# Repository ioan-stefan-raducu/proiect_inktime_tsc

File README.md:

# Proiect TSC 2026 - InkTime

Răducu Ioan Ștefan 335CA

## Descriere proiect
InkTime este un dispozitiv open source de tip smartwatch construit în cadrul clasei de proiectare hardware din UNSTPB. Device-ul are integrat un MCU nRF52840, senzori IMU și un display E-paper într-o carcasă compactă. Designul consideră aspectele legate de consum minim de energie și optimizarea PCB-ului pentru producție.

## Schema bloc

Se pot vedea în schema bloc componentele conectate prin săgeți. Săgețile au următoarele semnificații:
- **roșu** - trasee de putere
- **albastru deschis** - conexiuni I2C
- **albastru închis** - conexiuni SPI
- **mov** - trasee diferențiale
- **gri** - conexiuni GPIO sau fără a aparține categoriilor de mai sus

## Bill of Materials

| Componentă / Valoare | Cant. | Capsulă | Producător / Part Number | Sursă Achiziție (JLC/Mouser) | Datasheet |
| :--- | :---: | :--- | :--- | :--- | :--- |
| **nRF52840** | 1 | aQFN-73 | Nordic / nRF52840-QIAA | [Mouser Link](https://www.mouser.ro/c/?q=nRF52840) | [Datasheet](https://infocenter.nordicsemi.com/pdf/nRF52840_PS_v1.1.pdf) |
| **BMA423** | 1 | 12-pin LGA | Bosch / BMA423 | [Mouser Link](https://www.mouser.co.uk/ProductDetail/Bosch-Sensortec/BMA423?qs=HXFqYaX1Q2xC%252BSgeGoX3mg%3D%3D) | [Datasheet](https://www.bosch-sensortec.com/media/boschsensortec/downloads/datasheets/bst-bma423-ds004.pdf) |
| **BQ25180YBGR** | 1 | BGA-8 | TI / BQ25180YBGR | [Mouser Link](https://www.mouser.co.uk/ProductDetail/Texas-Instruments/BQ25180YBGR?qs=doiCPypUmgEWjAK%252BJAX6Tw%3D%3D) | [Datasheet](https://www.ti.com/lit/ds/symlink/bq25180.pdf) |
| **MAX17048G+T10** | 1 | TDFN-8 | Analog Devices / MAX17048 | [Mouser Link](https://www.mouser.ro/Search/Refine?Keyword=MAX17048G%2BT10) | [Datasheet](https://datasheets.maximintegrated.com/en/ds/MAX17048-MAX17049.pdf) |
| **DRV2605YZFR** | 1 | BGA-9 | TI / DRV2605YZFR | [Mouser Link](https://www.mouser.ro/Search/Refine?Keyword=DRV2605YZFR) | [Datasheet](https://www.ti.com/lit/ds/symlink/drv2605.pdf) |
| **RT6160AWSC** | 1 | WLCSP-15 | Richtek / RT6160AWSC | [Mouser Link](https://www.mouser.co.uk/ProductDetail/Richtek/RT6160AWSC?qs=amGC7iS6iy%2FLd9PSoixZXQ%3D%3D) | [Datasheet](https://www.richtek.com/assets/product_file/RT6160/DS6160-03.pdf) |
| **2450AT18B100E** | 1 | 3216 (1206) | Johanson / Antenă 2.45GHz | [Mouser Link](https://www.mouser.co.uk/ProductDetail/Johanson-Technology/2450AT18B100E?qs=yCnrNFeXz%252Bh5MFsFIXGZGA%3D%3D) | [Datasheet](https://www.johansontechnology.com/datasheets/2450AT18B100E/2450AT18B100E.pdf) |
| **744043680 (L4)** | 1 | 4.8x4.8mm | Wurth / 68µH Inductor | [JLC Part](https://jlcpcb.com/partdetail/Wurth_Elektronik-744043680/C167448) | [Datasheet](https://www.we-online.com/catalog/datasheet/744043680.pdf) |
| **FTC252012SR47** | 1 | 2520 (1008) | TDK / 0.47µH Inductor | [JLC Part (C5832368)](https://jlcpcb.com/partdetail/6763488-FTC252012SR47MBCA/C5832368) | [Datasheet](https://product.tdk.com/en/system/files/dam/doc/product/inductor/inductor/smd/catalog/inductor_commercial_power_ftc252012s_en.pdf) |
| **503480-2400** | 1 | FPC-24 | Molex / Conector EPD | [Mouser Link](https://www.mouser.co.uk/ProductDetail/Molex/503480-2400?qs=OAhjpuo3Vu7efIoxFh9AOw%3D%3D) | [Datasheet](https://www.molex.com/pdm_docs/sd/5034802400_sd.pdf) |
| **USB-C 16P** | 1 | SMT | Kinghelm / KH-TYPE-C-16P | [JLC Part](https://jlcpcb.com/partdetail/Kinghelm-KH_TYPE_C_16P/C5186522) | [Datasheet](https://datasheet.lcsc.com/lcsc/2112151030_Kinghelm-KH-TYPE-C-16P_C2930266.pdf) |
| **EVP-AKE31A** | 3 | SMT (Buton) | Panasonic / Tactile SW | [Mouser Link](https://www.mouser.ro/Search/Refine?Keyword=EVP-AKE31A) | [Datasheet](https://industrial.panasonic.com/ww/products/pt/tactile-sw/models/EVPAKE31A) |
| **USBLC6-2SC6Y** | 1 | SOT-23-6 | ST / Protecție ESD | [JLC Part](https://jlcpcb.com/partdetail/STMicroelectronics-USBLC6_2SC6Y/C7519) | [Datasheet](https://www.st.com/resource/en/datasheet/usblc6-2.pdf) |
| **MBR0530** | 3 | SOD-123 | ON Semi / Schottky 0.5A | [JLC Part](https://jlcpcb.com/partdetail/onsemi-MBR0530T1G/C2131) | [Datasheet](https://www.onsemi.com/pdf/datasheet/mbr0530t1-d.pdf) |
| **SI1308EDL** | 1 | SC-70-3 | Vishay / N-Ch MOSFET | [Mouser Link](https://www.mouser.ro/Search/Refine?Keyword=SI1308EDL) | [Datasheet](https://www.vishay.com/docs/72013/si1308edl.pdf) |
| **DMG2305UX-7** | 1 | SOT-23 | Diodes Inc / P-Ch MOSFET | [JLC Part](https://jlcpcb.com/partdetail/Diodes_Incorporated-DMG2305UX_7/C128526) | [Datasheet](https://www.diodes.com/assets/Datasheets/DMG2305UX.pdf) |

### Rezistente si condensatoare

| Valoare | Cant. | Capsulă | Tip | JLC |
| :--- | :---: | :--- | :--- | :--- |
| **1uF / 50V** | 10 | 0402 | Condensator (EPD) | [C52923](https://jlcpcb.com/partdetail/Samsung_Electro_Mechanics-CL05A105KB5NQNC/C52923) |
| **10uF** | 4 | 0402 | Condensator | [C15525](https://jlcpcb.com/partdetail/Samsung_Electro_Mechanics-CL05A106MQ5NUNC/C15525) |
| **100nF** | 5 | 0201 | Condensator | [C1619](https://jlcpcb.com/partdetail/Murata_Electronics-GRM033R61A104KE84D/C1619) |
| **10K** | 6 | 0201 | Rezistență | [C25744](https://jlcpcb.com/partdetail/Yageo-RC0201JR_0710KL/C25744) |
| **5.1K (5K1)** | 2 | 0201 | Rezistență (USB CC) | [C25785](https://jlcpcb.com/partdetail/Yageo-RC0201JR_075K1L/C25785) |
| **3.3K (3K3)** | 2 | 0201 | Rezistență | [C25891](https://jlcpcb.com/partdetail/Yageo-RC0201JR_073K3L/C25891) |

## Funcționalități hardware

Pentru următoarele funcționalități hardware se vor folosi numele circuitelor așa cum sunt reprezentate în schematic. La conectarea cu alte circuite se vor menționa circuitele cu semnalele puse în paranteză, lângă menționarea lor.

### LiPo Battery
Circuitul LiPo battery este conectorul către baterie. El este amplasat aproape de circuitul **DC/DC (VREG, 3V3)** și **Fuel Gauge (3V3, VBAT)**, formând un ansamblu. Acest ansamblu este amplasat lângă **E-Paper Connector** și **USB Connector (VBUS)** pentru a izola zonele care se ocupă cu traseele de putere sau au putere mare de restul componentelor, pentru a evita interferențele. Este conectat la microcontroler prin protocolul I2C.

### Fuel Gauge
Circuitul Fuel Gauge se ocupă cu măsurarea nivelului bateriei și alertarea microprocesorului când bateria este descărcată. El este conectat la microcontroler prin protocolul I2C și semnalul **ALERT** (probabil folosit ca întrerupere).

### DC/DC
Circuitul DC/DC este adaptorul de tensiune al PCB-ului. El trimite semnale de putere folosind PWM pentru a regla tensiunea. Este conectat la procesor prin protocolul I2C.

### E-Paper Connector
Circuitul E-Paper Connector este conexiunea la ecranul E-Paper. El este conectat la microcontroler prin protocolul SPI. Semnalele care sunt conectate la microcontroler sunt **EPD_BUSY, EPD_RST, EPD_DC, EPD_CS, SCK și MOSI**. El este conectat și la circuitul **E-Paper Drive Circuit** prin PREVGH, PREVGL și 3V3.

### E-Paper Drive Circuit
Circuitul E-Paper Drive "crește” semnalul pentru modelarea cernelii pentru ecranul E-Paper. El este plasat direct lângă **E-Paper Display Connector** datorită semnalului puternic de putere (până la 50V) pe care îl transmite ecranului. Astfel, ansamblul de putere menționat mai devreme, conectorul E-Paper și acest circuit sunt puse apropiat pentru a nu interfera cu restul PCB-ului.

### USB-C Connector
Circuitul USB-C Connector reprezintă mufa USB. Este conectat la ansamblul de putere (VBUS) și la circuitul **ESD Protection (VBUS, DN, DP)**. Deși în designul PCB-ului DN și DP ar trebui să fie trasee diferențiale, ele nu sunt. Am luat această decizie datorită poziției apropiate a USB-C Connector față de circuitul ESD Protection. El este conectat la microcontroler prin semnalul VBUS și indirect, prin ESD Protection, prin semnalele diferențiale D+ și D-.

### ESD Protection
Circuitul ESD Protection reprezintă protecția mufei USB-C în cazul descărcărilor statice. El este conectat la **USB-C Connector (VBUS, DN, DP)** și la microcontroler (D+, D- trasee diferențiale). În designul PCB-ului, semnalele D+ și D- au aceeași lungime.

### SWD
Circuitul SWD este folosit pentru debugging și este conectat la semnalele importante (**RESET, 3V3 și GND**). Poate fi conectat la JTAG.

### Haptic Driver
Circuitul Haptic Driver este cel responsabil de vibrația ceasului. El este conectat la microcontroler prin protocolul I2C și semnalul **HAPTIC_EN**. În PCB, el este situat la distanță de IMU pentru a nu interfera cu acesta în momentul în care vibrează.

### IMU
Circuitul IMU măsoară accelerația și direcția ceasului pentru a determina câți pași a făcut utilizatorul. El este amplasat departe de Haptic Driver pentru motivul menționat mai sus și spre centrul ceasului pentru a măsura cât mai precis pașii (mișcarea ceasului pe mână poate afecta măsurătorile). El este conectat la microcontroler prin I2C și semnalele **IMUINT1 și IMUINT2** (întreruperi ce pot fi setate).

## Descrierea conexiunilor microcontrolerului nRF52840

* **P$AD22 (SWO)** - conexiune cu TP_SWO pentru debug.
* **P$AC13 (RESET)** - conexiune cu TP_RESET și SWD pentru resetarea componentei.
* **P$AD12 (EPD_BUSY)** - conexiune cu E-Paper Display (EPD_BUSY). Indică dacă ecranul este ocupat cu afișarea sau nu.
* **P$AD10 (EPD_DC)** - conexiune cu E-Paper Display (EPD_DC - Data/Command). Descrie dacă bitul trimis este pentru date (pixeli) sau o comandă.
* **P$K2 (EPD_CS)** - conexiune cu E-Paper Display (EPD_CS - Chip Select) pentru protocolul SPI.
* **P$AD12 (EPD_RST)** - conexiune cu E-Paper Display (EPD_RST) pentru resetare.
* **P$AC9 (P0.14)** - GPIO buton din mijloc.
* **P$AD8 (P0.13)** - GPIO buton din dreapta.
* **P$W24 (P1.02)** - GPIO buton din stânga.
* **P$AD6 (D+)** - traseu diferențial pozitiv către ESD Protection.
* **P$AD4 (D-)** - traseu diferențial negativ către ESD Protection.
* **P$AD2 (VBUS)** - conexiune cu semnalul VBUS al USB-C Connector.
* **P$U1 (HAPTIC_EN)** - conexiune cu Haptic Driver pentru enable/disable.
* **P$T2 (PMIC_INT)** - conexiune întrerupere cu circuitul bateriei (LiPo Battery).
* **P$P2 (IMU_INT2)** - conexiune întrerupere cu IMU.
* **P$M2 (SCL)** - conexiune I2C între restul componentelor care folosesc acest protocol.
* **P$N1 (IMU_INT1)** - conexiune întrerupere cu IMU.
* **P$L1 (SDA)** - conexiune I2C cu restul componentelor care folosesc acest protocol.
* **P$F2 și P$D2** - conexiune cu ceasul de 32 kHz.
* **P$A12 (SCK)** - conexiune clock cu ecranul pentru protocolul SPI.
* **P$P13 (MOSI)** - MOSI pentru conexiunea SPI (cu ecranul).
* **P$A23 și P$A24** - conexiune cu ceasul de 32 MHz.
* **P$J24 (ALERT)** - conexiune cu alerta circuitului Fuel Gauge.
* **P$Y23 (P1.01)** - conexiune care conduce E-Paper Drive Circuit pentru a afișa cerneala pe ecran.
* **P$AA24 (SWDCLK)** - conexiune pentru SWD, cu scopul de debug al ceasului.
* **P$AC24 (SWDIO)** - conexiune SWD input/output.
* **P$H23, P$F23** - conexiune pentru transmiterea wireless prin antenă.

## Aprobarea erorilor și alte detalii

În afara erorilor de overlap deja aprobate la început (în total 6 erori), restul erorilor pot fi explicate astfel:
* **6 erori** de Solid Polygon Shape, Overlap, la butoane, apărute de la sincronizarea inițială a schematicului cu PCB-ul.
* **11 erori** de Via-SMD sau SMD-Via, Overlap, pentru via-in-pad a pinilor de pe procesor.

### Detalii post-review
* Am mutat circuitul **IMU** mai sus pentru a aloca suficient spațiu pe PCB pentru un via mai gros de la pinul 3V3 la stratul POWER. Pre-review se folosea un via cu grosimea de 0.2mm direct sub componenta IMU.
* Pentru a rezolva al doilea via cu grosimea de 0.2mm pentru un traseu de putere de la pinul P$AD23 al nRF52840, am alocat suficient spațiu pentru a avea grosimea indicată.
* La rezolvarea greșelii din schematic în care am folosit componenta **NORDIC_NRF_3_CAPACITOR** în locul componentei **GRM011R60J152KE01L** pentru condensatori, a apărut problema overlap cu fire de 0.3mm din cauza footprint-ului 0201 pe care îl are obligatoriu noua componentă. Pentru a rezolva, am variat grosimea la 0.25mm. Personal aș fi păstrat componenta precedentă datorită footprint-ului 0402.
* Am mutat firul **P0.14** de pe bottom pentru a nu trece sub ceasul de 32 kHz al procesorului.
* În urma modificării schematicului circuitului Haptic Driver, pinul **SDA** era plasat în mijloc. Pentru a rezolva problema, am folosit via-in-pad. De asemenea, a fost nevoie să conectez pinul GND și am folosit via către stratul GND.

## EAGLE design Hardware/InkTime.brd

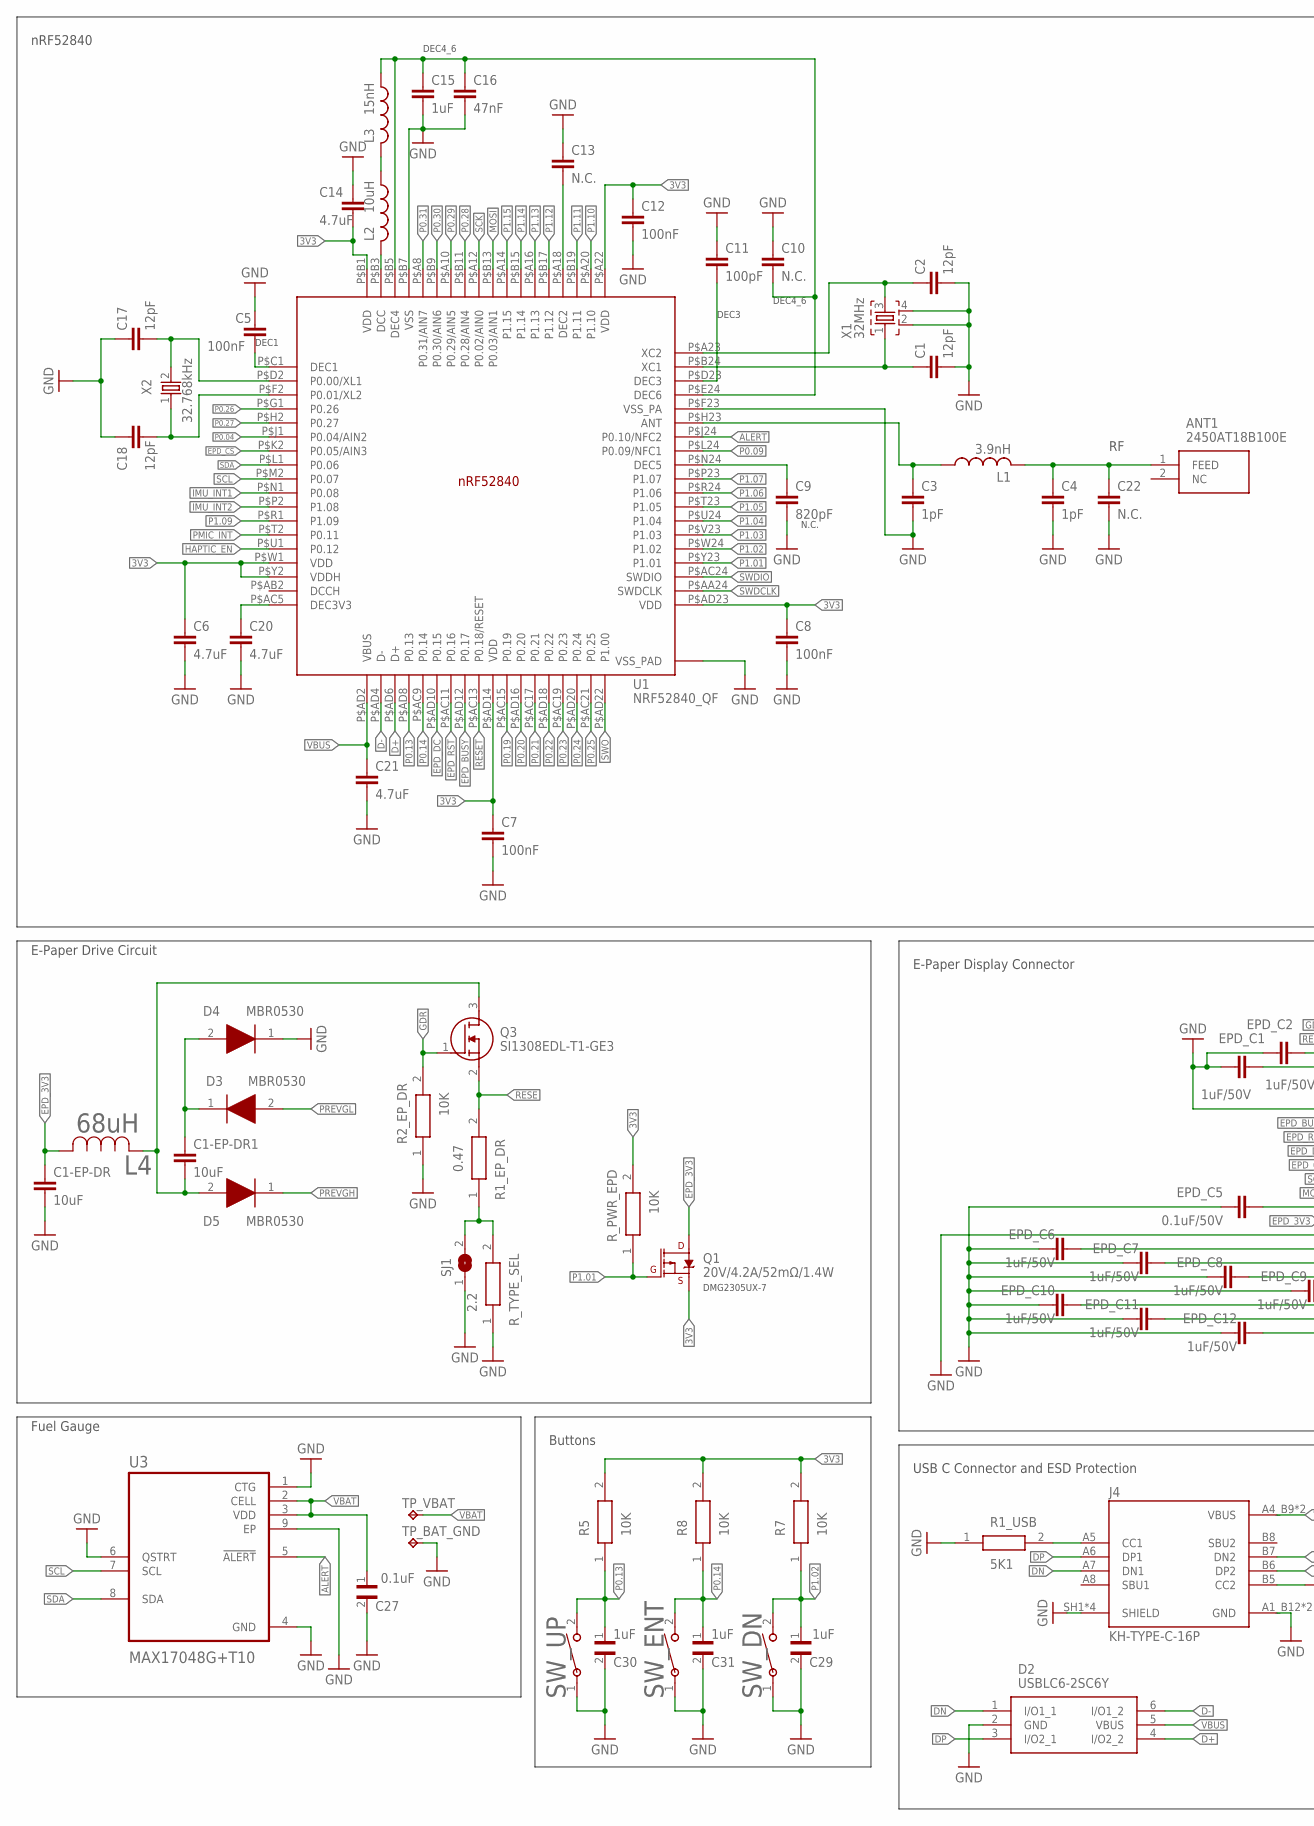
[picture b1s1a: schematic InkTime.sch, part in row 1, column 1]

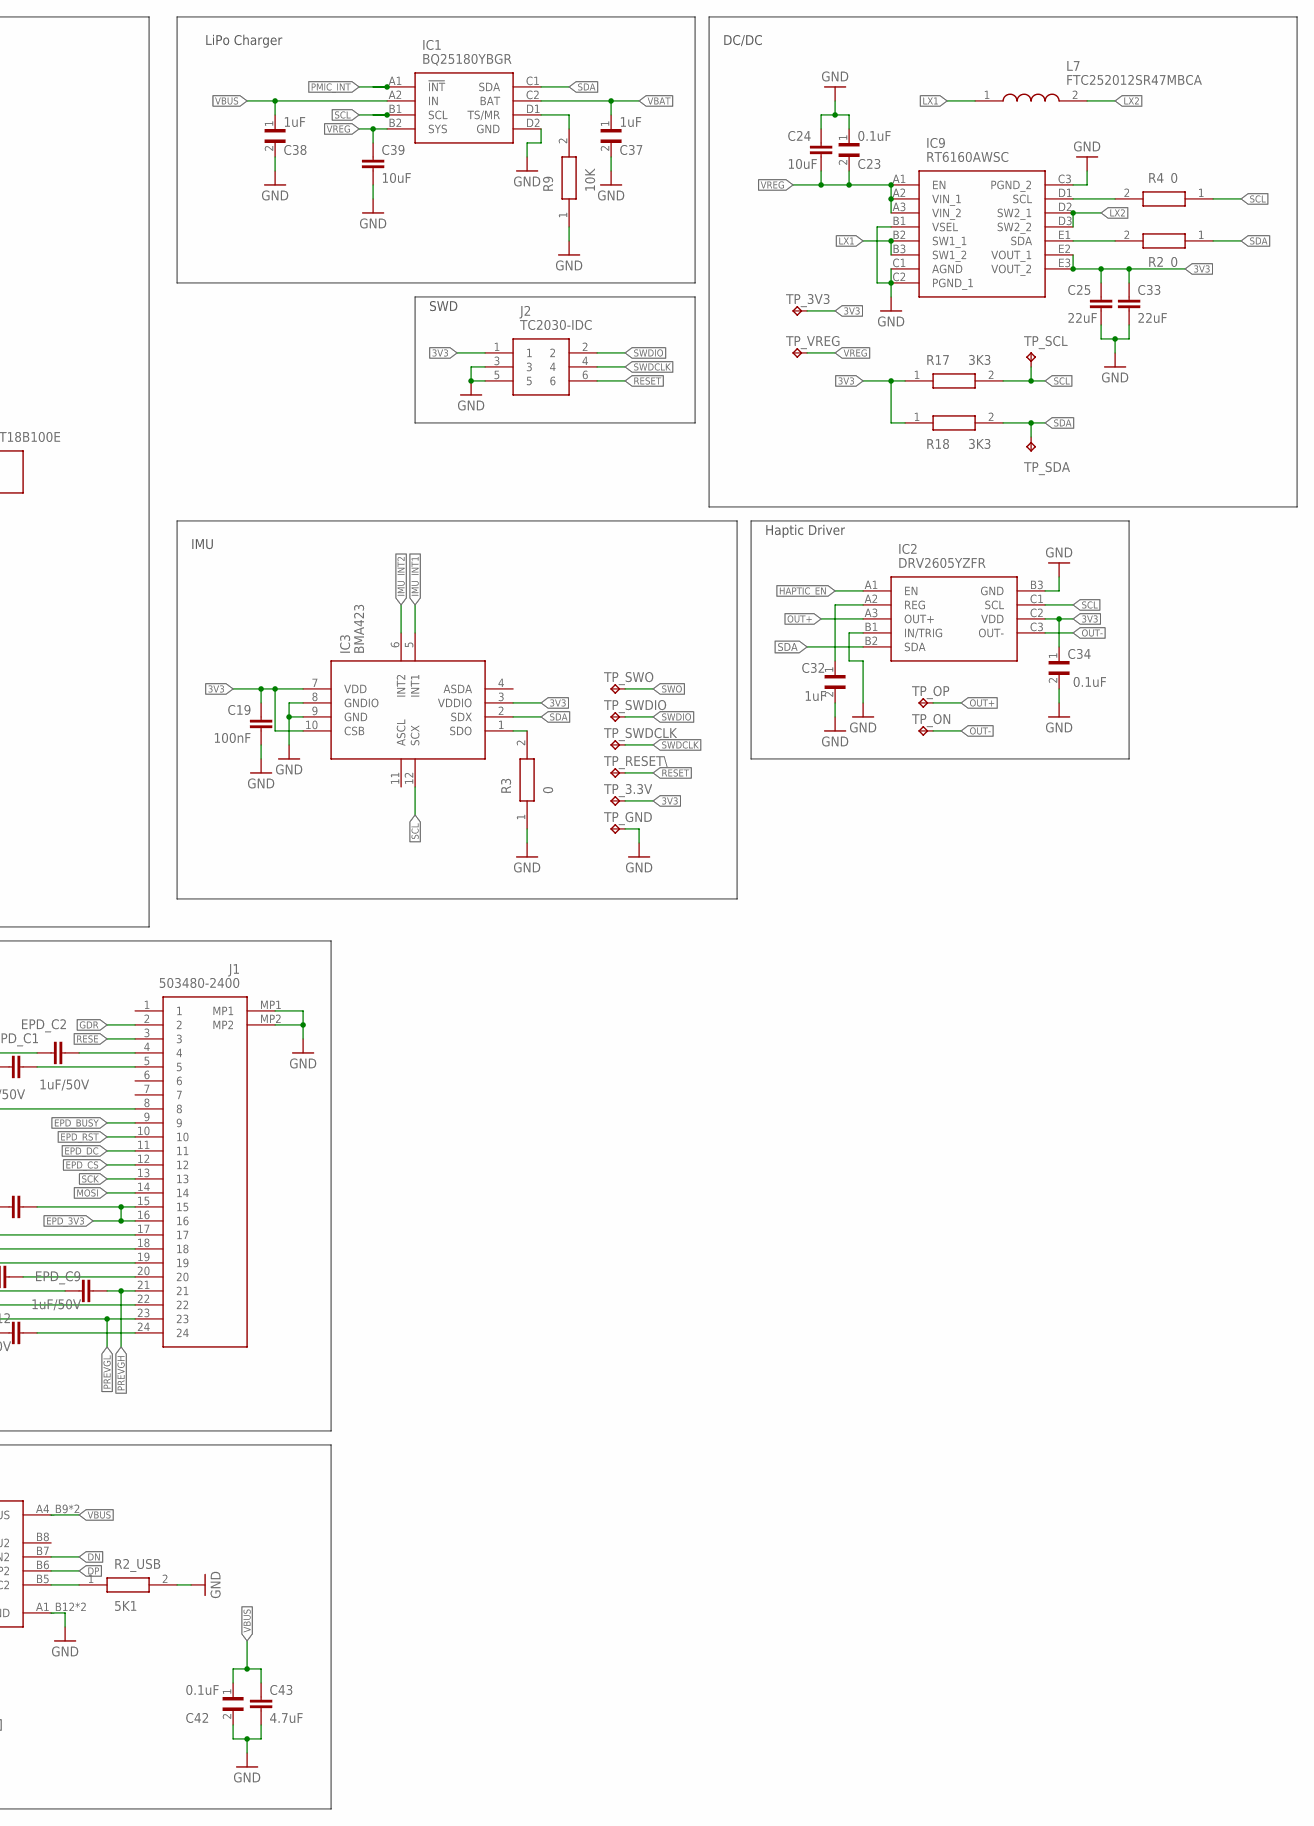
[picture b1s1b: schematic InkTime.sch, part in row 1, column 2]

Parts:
ANT1: 2450AT18B100E; 2450AT18B100E_ANTC3216X140N
C1, C2, C17, C18: 12pF; NORDIC_NRF_3_RESC0201_L
C1-EP-DR, C1-EP-DR1, C24, C39: 10uF; NORDIC_NRF_3_RESC0402_L
C3, C4: 1pF; NORDIC_NRF_3_RESC0201_L
C5, C7, C8, C12, C19: 100nF; NORDIC_NRF_3_RESC0201_L
C6, C14, C20, C21, C43: 4.7uF; NORDIC_NRF_3_RESC0402_L
C9: 820pF; NORDIC_NRF_3_RESC0201_L
C10, C13, C22: N.C.; NORDIC_NRF_3_RESC0201_L
C11: 100pF; NORDIC_NRF_3_RESC0201_L
C15: 1uF; NORDIC_NRF_3_RESC0402_L
C16: 47nF; NORDIC_NRF_3_RESC0201_L
C23, C27, C34, C42: 0.1uF; GRM011R60J152KE01L_2_CAPC0201X13N
C25, C33: 22uF; NORDIC_NRF_3_RESC0402_L
C29, C30, C31, C32, C37, C38: 1uF; GRM011R60J152KE01L_2_CAPC0201X13N
D2: USBLC6-2SC6Y; ESP32_C6_LIBRARY_3_SOT95P280X145-6N
D3, D4, D5: MBR0530; ESP32_C6_LIBRARY_5_SOD3716X135N
EPD_C1, EPD_C2, EPD_C6, EPD_C7, EPD_C8, EPD_C9, EPD_C10, EPD_C11, EPD_C12: 1uF/50V; NORDIC_NRF_3_RESC0402_L
EPD_C5: 0.1uF/50V; NORDIC_NRF_3_RESC0201_L
IC1: BQ25180YBGR; BQ25180YBGR_BGA8C40P2X4_100X155X50
IC2: DRV2605YZFR; DRV2605YZFR_BGA9C50P3X3_144X144X62
IC3: BMA423; BMA423_BMA423
IC9: RT6160AWSC; RT6160AWSC_BGA15C40P3X5_140X230X60
J1: 503480-2400; 503480-2400_5034802400
J2: TC2030-IDC; TC2030-IDC_TC2030IDC
J4: KH-TYPE-C-16P; KH-TYPE-C-16P_KINGHELM_KH-TYPE-C-16P
L1: 3.9nH; NORDIC_NRF_2_RESC0201_L
L2: 10uH; NORDIC_NRF_2_RESC0402_L
L3: 15nH; NORDIC_NRF_2_RESC0201_L
L4: 68uH; ESP32_C6_LIBRARY_2_IND_4828-WE-TPC_WRE
L7: FTC252012SR47MBCA; MLP2016SR47MT0S1_INDC2016X100N
Q1: 20V/4.2A/52mΩ/1.4W; ESP32_C6_LIBRARY_4_ESP32_C6_LIBRARY_4_ESP32_C6_LIBRARY_4_ES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
Q3: SI1308EDL-T1-GE3; ESP32_C6_LIBRARY_6_SOT65P210X110-3N
R1_EP_DR: 0.47; CPF0201D7K68C1_0201
R1_USB, R2_USB: 5K1; ERA-1AEB3401C_0201
R2, R3, R4: 0; CPF0201D7K68C1_0201
R2_EP_DR, R5, R7, R8, R9: 10K; CPF0201D7K68C1_0201
R17, R18: 3K3; CPF0201D7K68C1_0201
R_PWR_EPD: 10K; CPF0201D7K68C1_0201
R_TYPE_SEL: 2.2; CPF0201D7K68C1_0201
SJ1: JUMPER_SJ; ESP32_C6_LIBRARY_7_JUMPER_SJ
SW_DN: 2025-10-22_07-23-44_LIBRARY_EVP-AKE31ASW_EVP-AKE3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; 2025-10-22_07-23-44_LIBRARY_SW_EVP-AKE31A_PAN
SW_ENT: 2025-10-22_07-23-44_LIBRARY_EVP-AKE31ASW_EVP-AKE3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; 2025-10-22_07-23-44_LIBRARY_SW_EVP-AKE31A_PAN
SW_UP: 2025-10-22_07-23-44_LIBRARY_EVP-AKE31ASW_EVP-AKE3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; 2025-10-22_07-23-44_LIBRARY_SW_EVP-AKE31A_PAN
TP_3.3V, TP_3V3: HECTOR_WATCH_1_TPTP20R; HECTOR_WATCH_1_TP20R
TP_BAT_GND: HECTOR_WATCH_1_TPTP20R; HECTOR_WATCH_1_TP20R
TP_GND: HECTOR_WATCH_1_TPTP20R; HECTOR_WATCH_1_TP20R
TP_ON: HECTOR_WATCH_1_TPTP20R; HECTOR_WATCH_1_TP20R
TP_OP: HECTOR_WATCH_1_TPTP20R; HECTOR_WATCH_1_TP20R
TP_RESET\: HECTOR_WATCH_1_TPTP20R; HECTOR_WATCH_1_TP20R
TP_SCL: HECTOR_WATCH_1_TPTP20R; HECTOR_WATCH_1_TP20R
TP_SDA: HECTOR_WATCH_1_TPTP20R; HECTOR_WATCH_1_TP20R
TP_SWDCLK: HECTOR_WATCH_1_TPTP20R; HECTOR_WATCH_1_TP20R
TP_SWDIO: HECTOR_WATCH_1_TPTP20R; HECTOR_WATCH_1_TP20R
TP_SWO: HECTOR_WATCH_1_TPTP20R; HECTOR_WATCH_1_TP20R
TP_VBAT: HECTOR_WATCH_1_TPTP20R; HECTOR_WATCH_1_TP20R
TP_VREG: HECTOR_WATCH_1_TPTP20R; HECTOR_WATCH_1_TP20R
U1: NRF52840_QF; NORDIC_NRF_4_AQFN50P700X700X85_HS-74N
U3: MAX17048G+T10; ESP32_C6_LIBRARY_SON50P200X200X80-9N
X1: 32MHz; NORDIC_NRF_BT-XTAL_2016_N
X2: 32.768kHz; NORDIC_NRF_1_XTAL_3215_N

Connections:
3V3: C6.1, C7.1, C8.1, C12.1, C14.2, C19.1, C25.1, C33.1, C34.1, IC2.C2 (VDD), IC3.3 (VDDIO), IC3.7 (VDD), IC3.10 (CSB), IC9.E2 (VOUT_1), IC9.E3 (VOUT_2), J2.1, Q1.2 (S), R5.2, R7.2, R8.2, R17.1, R18.1, R_PWR_EPD.2, TP_3.3V.TP, TP_3V3.TP, U1.P$A22 (VDD), U1.P$AD14 (VDD), U1.P$AD23 (VDD), U1.P$B1 (VDD), U1.P$W1 (VDD), U1.P$Y2 (VDDH)
ALERT: U1.P$J24 (P0.10/NFC2), U3.5 (!ALERT)
D+: D2.4 (I/O2_2), U1.P$AD6 (D+)
D-: D2.6 (I/O1_2), U1.P$AD4 (D-)
DN: D2.1 (I/O1_1), J4.A7 (DN1), J4.B7 (DN2)
DP: D2.3 (I/O2_1), J4.A6 (DP1), J4.B6 (DP2)
EPD_3V3: C1-EP-DR.1, EPD_C5.1, J1.15, J1.16, L4.2, Q1.3 (D)
EPD_BUSY: J1.9, U1.P$AD12 (P0.17)
EPD_CS: J1.12, U1.P$K2 (P0.05/AIN3)
EPD_DC: J1.11, U1.P$AD10 (P0.15)
EPD_RST: J1.10, U1.P$AC11 (P0.16)
GDR: J1.2, Q3.1 (G), R2_EP_DR.2
GND: C1.2, C1-EP-DR.2, C2.2, C3.2, C4.2, C5.1, C6.2, C7.2, C8.2, C9.2, C10.1, C11.1, C12.2, C13.1, C14.1, C15.2, C16.2, C17.1, C18.1, C19.2, C20.2, C21.2, C22.2, C23.1, C24.1, C25.2, C27.2, C29.2, C30.2, C31.2, C32.2, C33.2, C34.2, C37.2, C38.2, C39.2, C42.2, C43.2, D2.2 (GND), D4.1 (K), EPD_C1.2, EPD_C2.2, EPD_C5.2, EPD_C6.2, EPD_C7.2, EPD_C8.2, EPD_C9.2, EPD_C10.2, EPD_C11.2, EPD_C12.2, IC1.D2 (GND), IC2.B1 (IN/TRIG), IC2.B3 (GND), IC3.8 (GNDIO), IC3.9 (GND), IC9.B1 (VSEL), IC9.C1 (AGND), IC9.C2 (PGND_1), IC9.C3 (PGND_2), J1.8, J1.17, J1.MP1, J1.MP2, J2.3, J2.5, J4.A1_B12 (GND), J4.A12_B1 (GND), J4.SH1 (SHIELD), J4.SH2 (SHIELD), J4.SH3 (SHIELD), J4.SH4 (SHIELD), R1_USB.1, R2_EP_DR.1, R2_USB.2, R3.1, R9.1, R_TYPE_SEL.1, SJ1.1, SW_DN.1, SW_ENT.1, SW_UP.1, TP_BAT_GND.TP, TP_GND.TP, U1.P$74 (VSS_PAD), U1.P$75 (VSS_PAD), U1.P$76 (VSS_PAD), U1.P$77 (VSS_PAD), U1.P$78 (VSS_PAD), U1.P$79 (VSS_PAD), U1.P$80 (VSS_PAD), U1.P$81 (VSS_PAD), U1.P$82 (VSS_PAD), U1.P$83 (VSS_PAD), U1.P$84 (VSS_PAD), U1.P$85 (VSS_PAD), U1.P$86 (VSS_PAD), U1.P$87 (VSS_PAD), U1.P$88 (VSS_PAD), U1.P$89 (VSS_PAD), U1.P$90 (VSS_PAD), U1.P$B7 (VSS), U1.P$F23 (VSS_PA), U3.1 (CTG), U3.4 (GND), U3.6 (QSTRT), U3.9 (EP), X1.2, X1.4
HAPTIC_EN: IC2.A1 (EN), U1.P$U1 (P0.12)
IMU_INT1: IC3.5 (INT1), U1.P$N1 (P0.08)
IMU_INT2: IC3.6 (INT2), U1.P$P2 (P1.08)
LX1: IC9.B2 (SW1_1), IC9.B3 (SW1_2), L7.1
LX2: IC9.D2 (SW2_1), IC9.D3 (SW2_2), L7.2
MOSI: J1.14, U1.P$B13 (P0.03/AIN1)
unnamed: IC1.D1 (TS/MR), R9.2
unnamed: J4.A5 (CC1), R1_USB.2
unnamed: C1-EP-DR1.2, D5.2 (A), L4.1, Q3.3 (D)
unnamed: IC3.1 (SDO), R3.2
unnamed: EPD_C2.1, J1.4
unnamed: EPD_C1.1, J1.5
unnamed: EPD_C12.1, J1.24
unnamed: IC9.D1 (SCL), R4.2
unnamed: EPD_C10.1, J1.22
unnamed: IC9.E1 (SDA), R2.2
unnamed: EPD_C8.1, J1.20
unnamed: EPD_C7.1, J1.19
unnamed: EPD_C6.1, J1.18
unnamed: C9.1, U1.P$N24 (DEC5)
unnamed: C3.1, L1.1, U1.P$H23 (ANT)
unnamed: ANT1.1 (FEED), C4.1, C22.1, L1.2
unnamed: C2.1, U1.P$A23 (XC2), X1.3
unnamed: C1.1, U1.P$B24 (XC1), X1.1
unnamed: C11.2, U1.P$D23 (DEC3)
unnamed: C13.2, U1.P$A18 (DEC2)
unnamed: L2.2, U1.P$B3 (DCC)
unnamed: L2.1, L3.2
unnamed: C10.2, C15.1, C16.1, L3.1, U1.P$B5 (DEC4), U1.P$E24 (DEC6)
unnamed: C5.2, U1.P$C1 (DEC1)
unnamed: C17.2, U1.P$D2 (P0.00/XL1), X2.2
unnamed: C18.2, U1.P$F2 (P0.01/XL2), X2.1
unnamed: C1-EP-DR1.1, D3.1 (K), D4.2 (A)
unnamed: J4.B5 (CC2), R2_USB.1
unnamed: C32.1, IC2.A2 (REG)
unnamed: R1_EP_DR.1, R_TYPE_SEL.2, SJ1.2
OUT+: IC2.A3 (OUT+), TP_OP.TP
OUT-: IC2.C3 (OUT-), TP_ON.TP
P0.04: U1.P$J1 (P0.04/AIN2)
P0.09: U1.P$L24 (P0.09/NFC1)
P0.13: C30.1, R5.1, SW_UP.2, U1.P$AD8 (P0.13)
P0.14: C31.1, R8.1, SW_ENT.2, U1.P$AC9 (P0.14)
P0.19: U1.P$AC15 (P0.19)
P0.20: U1.P$AD16 (P0.20)
P0.21: U1.P$AC17 (P0.21)
P0.22: U1.P$AD18 (P0.22)
P0.23: U1.P$AC19 (P0.23)
P0.24: U1.P$AD20 (P0.24)
P0.25: U1.P$AC21 (P0.25)
P0.26: U1.P$G1 (P0.26)
P0.27: U1.P$H2 (P0.27)
P0.28: U1.P$B11 (P0.28/AIN4)
P0.29: U1.P$A10 (P0.29/AIN5)
P0.30: U1.P$B9 (P0.30/AIN6)
P0.31: U1.P$A8 (P0.31/AIN7)
P1.01: Q1.1 (G), R_PWR_EPD.1, U1.P$Y23 (P1.01)
P1.02: C29.1, R7.1, SW_DN.2, U1.P$W24 (P1.02)
P1.03: U1.P$V23 (P1.03)
P1.04: U1.P$U24 (P1.04)
P1.05: U1.P$T23 (P1.05)
P1.06: U1.P$R24 (P1.06)
P1.07: U1.P$P23 (P1.07)
P1.09: U1.P$R1 (P1.09)
P1.10: U1.P$A20 (P1.10)
P1.11: U1.P$B19 (P1.11)
P1.12: U1.P$B17 (P1.12)
P1.13: U1.P$A16 (P1.13)
P1.14: U1.P$B15 (P1.14)
P1.15: U1.P$A14 (P1.15)
P$AC5: C20.1, U1.P$AC5 (DEC3V3)
PMIC_INT: IC1.A1 (!INT), U1.P$T2 (P0.11)
PREVGH: D5.1 (K), EPD_C9.1, J1.21
PREVGL: D3.2 (A), EPD_C11.1, J1.23
RESE: J1.3, Q3.2 (S), R1_EP_DR.2
RESET: J2.6, TP_RESET\.TP, U1.P$AC13 (P0.18/RESET)
SCK: J1.13, U1.P$A12 (P0.02/AIN0)
SCL: IC1.B1 (SCL), IC2.C1 (SCL), IC3.12 (SCX), R4.1, R17.2, TP_SCL.TP, U1.P$M2 (P0.07), U3.7 (SCL)
SDA: IC1.C1 (SDA), IC2.B2 (SDA), IC3.2 (SDX), R2.1, R18.2, TP_SDA.TP, U1.P$L1 (P0.06), U3.8 (SDA)
SWDCLK: J2.4, TP_SWDCLK.TP, U1.P$AA24 (SWDCLK)
SWDIO: J2.2, TP_SWDIO.TP, U1.P$AC24 (SWDIO)
SWO: TP_SWO.TP, U1.P$AD22 (P1.00)
VBAT: C27.1, C37.1, IC1.C2 (BAT), TP_VBAT.TP, U3.2 (CELL), U3.3 (VDD)
VBUS: C21.1, C38.1, C42.1, C43.1, D2.5 (VBUS), IC1.A2 (IN), J4.A4_B9 (VBUS), J4.A9_B4 (VBUS), U1.P$AD2 (VBUS)
VREG: C23.2, C24.2, C39.1, IC1.B2 (SYS), IC9.A1 (EN), IC9.A2 (VIN_1), IC9.A3 (VIN_2), TP_VREG.TP

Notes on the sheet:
DEC4_6
DEC3
DEC1
N.C.
DEC4_6
DMG2305UX-7
LiPo Charger
DC/DC
nRF52840
Buttons
IMU
SWD
E-Paper Drive Circuit
Fuel Gauge
E-Paper Display Connector
USB C Connector and ESD Protection
Haptic Driver

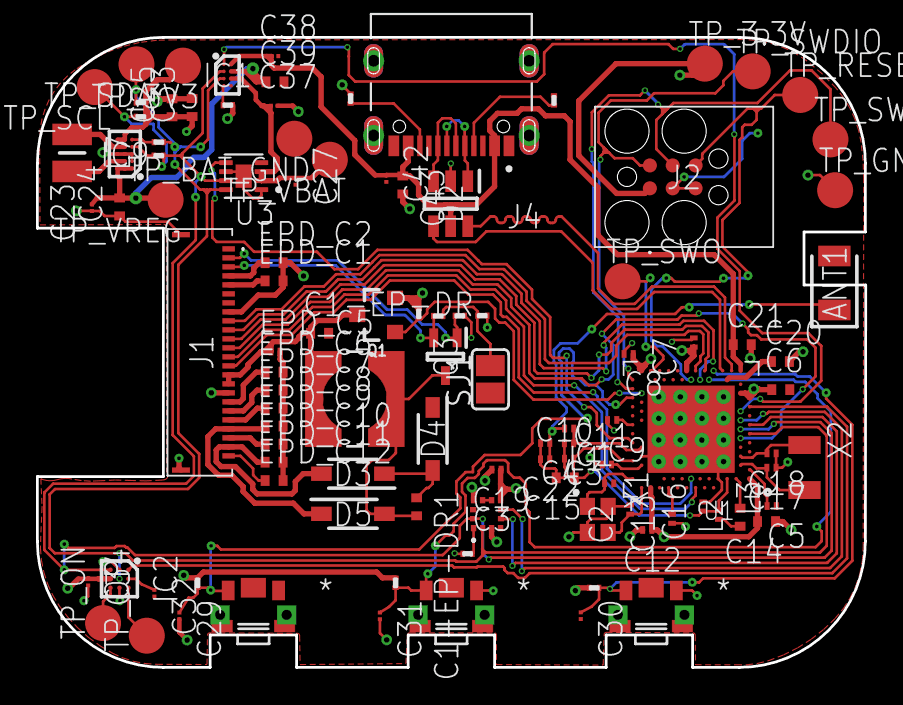
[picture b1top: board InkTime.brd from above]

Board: 4 copper layers, 46.0 x 35.0 mm, 105 parts (0 on the bottom side), 70 nets.

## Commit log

2026-04-19 Fixed #1. Added README.md, and updated the schematic and PCB design as stated in the issue.
2026-04-19 Finishing touches to README.md by better formatting it and added diacritics.

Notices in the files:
parts and their libraries:
COPYRIGHT: Copyright (C) 2024 Ultra Librarian. All rights reserved.
COPYRIGHT: Copyright (C) 2025 Ultra Librarian. All rights reserved.
